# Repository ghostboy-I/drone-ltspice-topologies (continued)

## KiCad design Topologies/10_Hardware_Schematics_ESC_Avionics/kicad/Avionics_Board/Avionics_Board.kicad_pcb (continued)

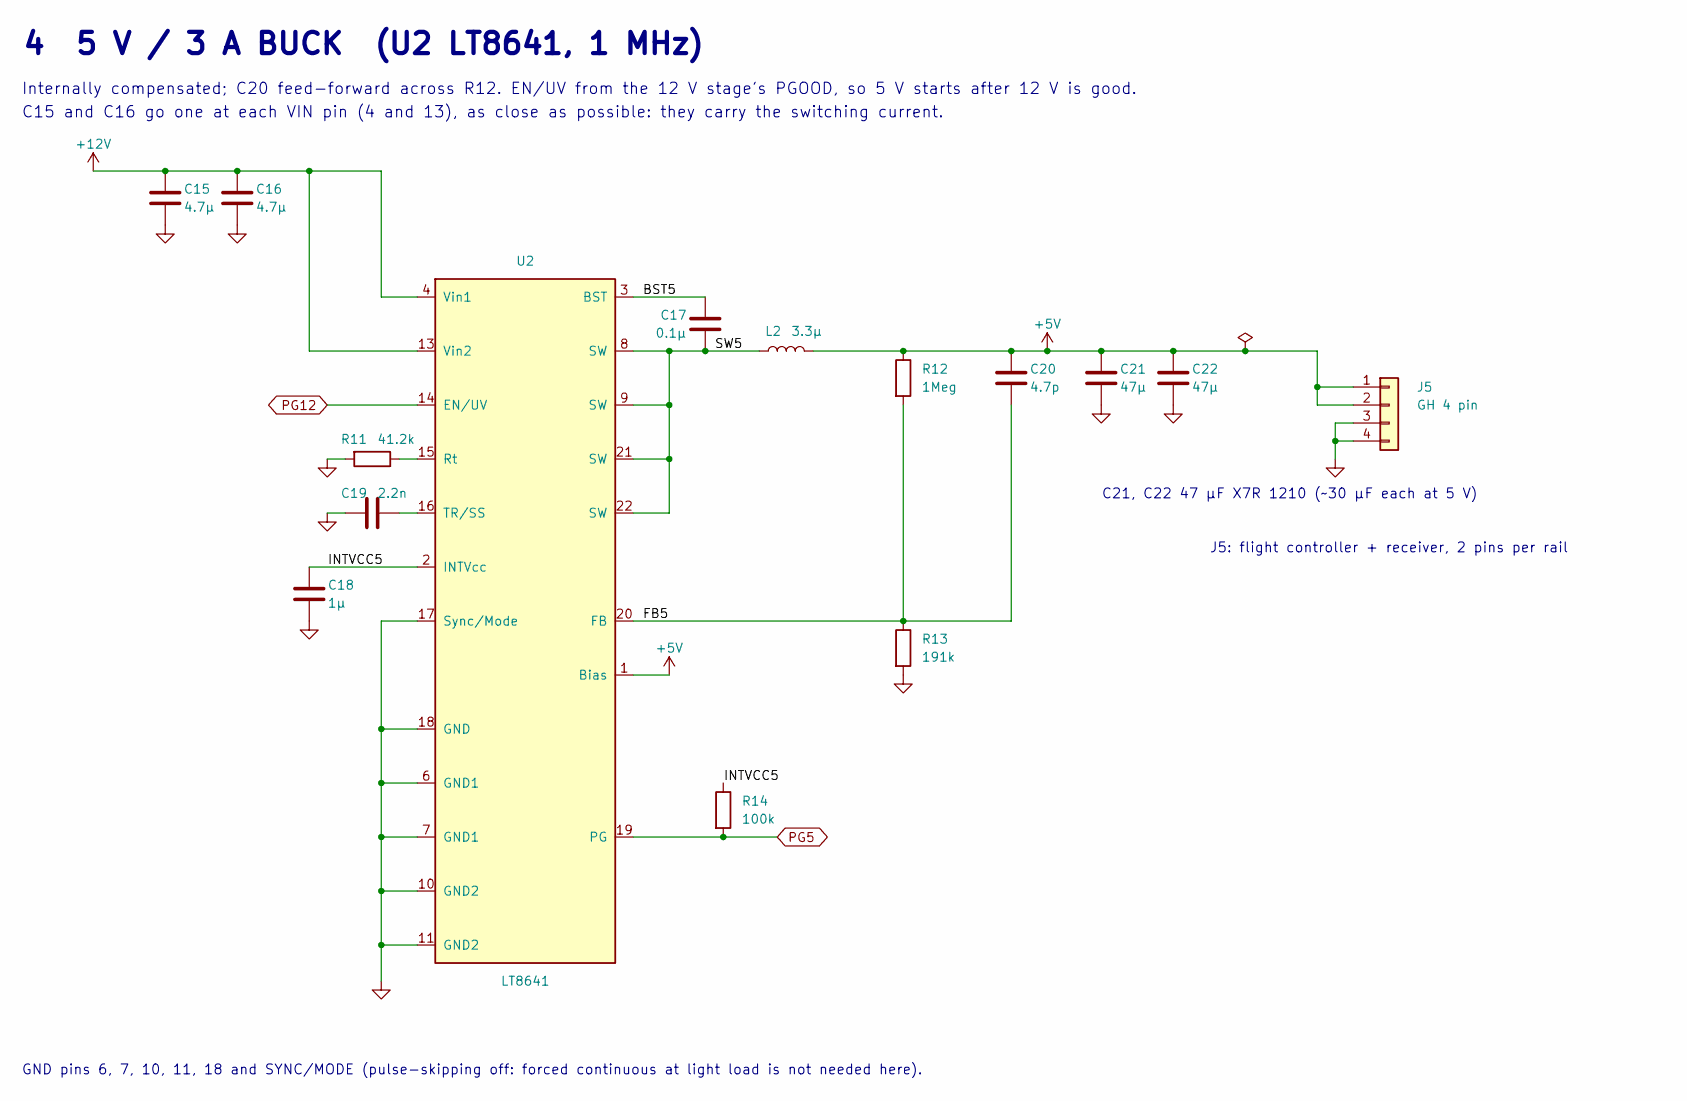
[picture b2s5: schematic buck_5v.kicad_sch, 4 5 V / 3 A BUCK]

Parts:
C15, C16: 4.7µ; C_0805_2012Metric; Rating 25 V; MPN/Spec X7R
C17: 0.1µ; C_0603_1608Metric; MPN/Spec X7R
C18: 1µ; C_0603_1608Metric; MPN/Spec X7R
C19: 2.2n; C_0603_1608Metric; MPN/Spec X7R
C20: 4.7p; C_0603_1608Metric; MPN/Spec X7R
C21, C22: 47µ; C_1210_3225Metric; Rating 10 V; MPN/Spec X7R 1210 (~30 µF at 5 V)
J5: GH 4 pin; JST_GH_BM04B-GHS-TBT_1x04-1MP_P1.25mm_Vertical; MPN/Spec JST GH 4 pin (2 pins per rail, 1 A/pin)
L2: 3.3µ; L_Coilcraft_XAL4020-XXX; Rating Isat 6 A; MPN/Spec shielded, Isat ≥ 6 A, DCR ≤ 10 mΩ
R11: 41.2k; R_0603_1608Metric; MPN/Spec 1 %, thick film
R12: 1Meg; R_0603_1608Metric; MPN/Spec 1 %, thick film
R13: 191k; R_0603_1608Metric; MPN/Spec 1 %, thick film
R14: 100k; R_0603_1608Metric; MPN/Spec 1 %, thick film
U2: LT8641; Linear_UDC-18-2EP_3x4mm_P0.5mm; Rating 65 V; MPN/Spec LT8641EUDC#PBF (UDC 20(18)-lead 3x4 mm 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

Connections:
+5V: C20.1, C21.1, C22.1, J5.1, J5.2, L2.2, R12.1, U2.1 (Bias); also elsewhere on the board
+12V: C15.1, C16.1, U2.4 (Vin1), U2.13 (Vin2); also elsewhere on the board
/Buck_5V/BST5: C17.1, U2.3 (BST)
/Buck_5V/FB5: C20.2, R12.2, R13.1, U2.20 (FB)
/Buck_5V/INTVCC5: C18.1, R14.1, U2.2 (INTVcc)
/Buck_5V/SW5: C17.2, L2.1, U2.8 (SW), U2.9 (SW), U2.21 (SW), U2.22 (SW)
GND: C15.2, C16.2, C18.2, C19.2, C21.2, C22.2, J5.3, J5.4, R11.2, R13.2, U2.6 (GND1), U2.7 (GND1), U2.10 (GND2), U2.11 (GND2), U2.17 (Sync/Mode), U2.18 (GND); also elsewhere on the board
unnamed: R11.1, U2.15 (Rt)
unnamed: C19.1, U2.16 (TR/SS)
PG5: R14.2, U2.19 (PG); also elsewhere on the board
PG12: U2.14 (EN/UV); also elsewhere on the board

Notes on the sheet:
4 5 V / 3 A BUCK (U2 LT8641, 1 MHz)
Internally compensated; C20 feed-forward across R12. EN/UV from the 12 V stage's PGOOD, so 5 V starts after 12 V is good.
C15 and C16 go one at each VIN pin (4 and 13), as close as possible: they carry the switching current.
GND pins 6, 7, 10, 11, 18 and SYNC/MODE (pulse-skipping off: forced continuous at light load is not needed here).
C21, C22 47 µF X7R 1210 (~30 µF each at 5 V)
J5: flight controller + receiver, 2 pins per rail

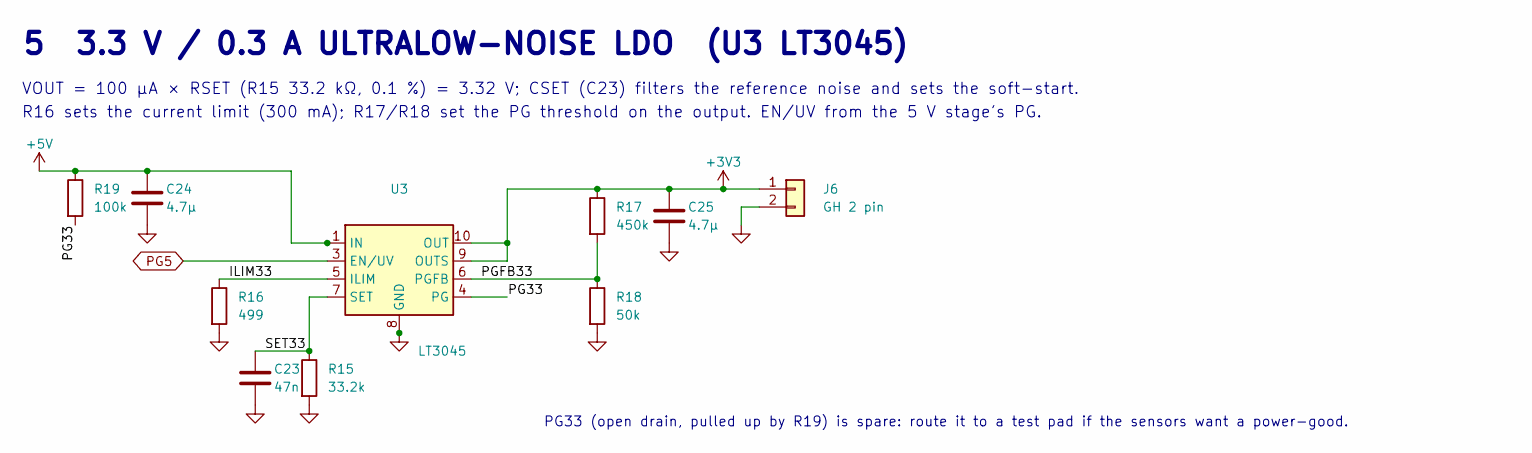
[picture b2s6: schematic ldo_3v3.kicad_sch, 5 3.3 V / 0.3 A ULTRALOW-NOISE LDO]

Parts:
C23: 47n; C_0603_1608Metric; MPN/Spec X7R
C24, C25: 4.7µ; C_0805_2012Metric; Rating 10 V; MPN/Spec X7R
J6: GH 2 pin; JST_GH_BM02B-GHS-TBT_1x02-1MP_P1.25mm_Vertical; MPN/Spec JST GH 2 pin
R15: 33.2k; R_0603_1608Metric; MPN/Spec 0.1 %, 25 ppm
R16: 499; R_0603_1608Metric; MPN/Spec 1 %, thick film
R17: 450k; R_0603_1608Metric; MPN/Spec 1 %, thick film
R18: 50k; R_0603_1608Metric; MPN/Spec 1 %, thick film
R19: 100k; R_0603_1608Metric; MPN/Spec 1 %, thick film
U3: LT3045; DFN-10-1EP_3x3mm_P0.5mm_EP1.65x2.38mm; Rating 20 V; MPN/Spec LT3045EDD (DFN-10 3x3)

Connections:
+3V3: C25.1, J6.1, R17.1, U3.9 (OUTS), U3.10 (OUT)
+5V: C24.1, R19.1, U3.1 (IN), U3.2 (IN); also elsewhere on the board
/LDO_3V3/ILIM33: R16.1, U3.5 (ILIM)
/LDO_3V3/PG33: R19.2, U3.4 (PG)
/LDO_3V3/PGFB33: R17.2, R18.1, U3.6 (PGFB)
/LDO_3V3/SET33: C23.1, R15.1, U3.7 (SET)
GND: C23.2, C24.2, C25.2, J6.2, R15.2, R16.2, R18.2, U3.8 (GND), U3.11 (GND); also elsewhere on the board
PG5: U3.3 (EN/UV); also elsewhere on the board

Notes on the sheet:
5 3.3 V / 0.3 A ULTRALOW-NOISE LDO (U3 LT3045)
VOUT = 100 µA × RSET (R15 33.2 kΩ, 0.1 %) = 3.32 V; CSET (C23) filters the reference noise and sets the soft-start.
R16 sets the current limit (300 mA); R17/R18 set the PG threshold on the output. EN/UV from the 5 V stage's PG.
PG33 (open drain, pulled up by R19) is spare: route it to a test pad if the sensors want a power-good.

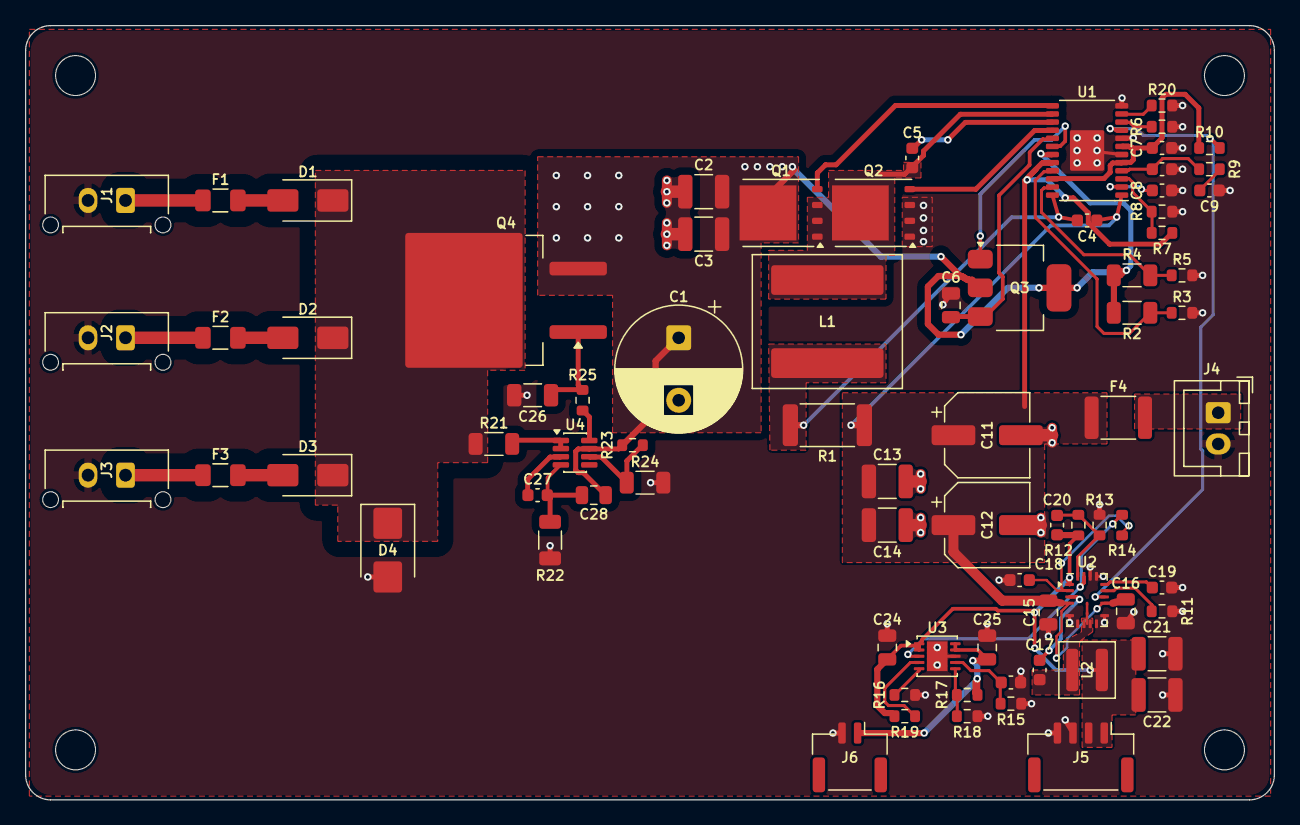
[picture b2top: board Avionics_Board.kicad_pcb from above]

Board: 4 copper layers, 100.0 x 62.0 mm, 81 parts (0 on the bottom side), 47 nets.

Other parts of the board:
H1, H2, H3, H4: M3; MountingHole_3.2mm_M3

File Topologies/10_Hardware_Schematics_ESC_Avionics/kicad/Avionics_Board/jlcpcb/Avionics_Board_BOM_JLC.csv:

Comment,Designator,Footprint,LCSC Part #
"33u Aluminium electrolytic, low ESR 160 V",C1,CP_Radial_D10.0mm_P5.00mm,
2.2u X7R 1210 250 V,"C2,C3",C_1210_3225Metric,
1n X7R,C4,C_0603_1608Metric,
0.1u X7R 25 V,C5,C_0603_1608Metric,
4.7u X7R 25 V,"C6,C15,C16",C_0805_2012Metric,
0.1u X7R,"C7,C17",C_0603_1608Metric,
33n X7R,C8,C_0603_1608Metric,
15n X7R,C9,C_0603_1608Metric,
330p X7R,C10,C_0603_1608Metric,
"47u Polymer, ESR <= 15 mR 25 V","C11,C12",CP_Elec_6.3x7.7,
10u 10 uF X7R 1210 (5 uF at 12 V bias) 25 V,"C13,C14",C_1210_3225Metric,
1u X7R,C18,C_0603_1608Metric,
2.2n X7R,C19,C_0603_1608Metric,
4.7p X7R,C20,C_0603_1608Metric,
47u X7R 1210 (~30 uF at 5 V) 10 V,"C21,C22",C_1210_3225Metric,
47n X7R,C23,C_0603_1608Metric,
4.7u X7R 10 V,"C24,C25",C_0805_2012Metric,
10n X7R 1206 250 V (e.g. Murata GRM31BR72E103KW01) 250 V,C26,C_1206_3216Metric,
180n X7R,C27,C_0603_1608Metric,
470n X7R 25 V,C28,C_0805_2012Metric,
ES1D ES1D 200 V 1 A,"D1,D2,D3",D_SMA,
SMBJ110A SMBJ110A VBR 122 V,D4,D_SMB,
"0.5 A Littelfuse 0451.500 (NANO2, 125 V DC) 125 V DC","F1,F2,F3",Fuse_1206_3216Metric,
"2 A Bourns MF-MSMF200 (1812) 2 A hold, 16 V",F4,Fuse_1812_4532Metric,
"Micro-Fit 3.0 Molex Micro-Fit 3.0, 2 pin (600 V, 5 A) >=150 V","J1,J2,J3",Molex_Micro-Fit_3.0_43650-0215_1x02_P3.00mm_Vertical,
XH 2 pin JST XH 2 pin (3 A),J4,JST_XH_B2B-XH-A_1x02_P2.50mm_Vertical,
"GH 4 pin JST GH 4 pin (2 pins per rail, 1 A/pin)",J5,JST_GH_BM04B-GHS-TBT_1x04-1MP_P1.25mm_Vertical,
GH 2 pin JST GH 2 pin,J6,JST_GH_BM02B-GHS-TBT_1x02-1MP_P1.25mm_Vertical,
"47u shielded 10x10 mm (e.g. Coilcraft XAL1010 family), Isat >= 9.2 A, DCR <= 30 mR Isat 9.2 A",L1,L_Coilcraft_XAL1010-XXX,
"3.3u shielded, Isat >= 6 A, DCR <= 10 mR Isat 6 A",L2,L_Coilcraft_XAL4020-XXX,
BSC520N15NS3 Infineon BSC520N15NS3 150 V 21 A,Q1,TDSON-8-1,
BSC360N15NS3 Infineon BSC360N15NS3 150 V 30 A,Q2,TDSON-8-1,
BSP89 Infineon BSP89 240 V,Q3,SOT-223-3_TabPin2,
"FDB33N25 onsemi FDB33N25 (250 V, 94 mR, D2PAK) 250 V 33 A",Q4,TO-263-2,
"10m current sense, 1 %, 1 W 1 W",R1,R_2512_6332Metric,
"976k 1 %, thick film 200 V",R2,R_1206_3216Metric,
"20k 1 %, thick film",R3,R_0603_1608Metric,
"1Meg 1 %, thick film 200 V",R4,R_1206_3216Metric,
"10.2k 1 %, thick film",R5,R_0603_1608Metric,
"30.1k 1 %, thick film",R6,R_0603_1608Metric,
"140k 1 %, thick film",R7,R_0603_1608Metric,
"10k 1 %, thick film",R8,R_0603_1608Metric,
"6.98k 1 %, thick film",R9,R_0603_1608Metric,
"100k 1 %, thick film","R10,R14,R19,R20",R_0603_1608Metric,
"41.2k 1 %, thick film",R11,R_0603_1608Metric,
"1Meg 1 %, thick film",R12,R_0603_1608Metric,
"191k 1 %, thick film",R13,R_0603_1608Metric,
"33.2k 0.1 %, 25 ppm",R15,R_0603_1608Metric,
"499 1 %, thick film",R16,R_0603_1608Metric,
"450k 1 %, thick film",R17,R_0603_1608Metric,
"50k 1 %, thick film",R18,R_0603_1608Metric,
"2.49Meg 1 %, thick film 200 V",R21,R_1206_3216Metric,
"274k 1 %, thick film 200 V",R22,R_1206_3216Metric,
"12.4k 1 %, thick film",R23,R_0603_1608Metric,
"1.15Meg 1 %, thick film 200 V",R24,R_1206_3216Metric,
"10 1 %, thick film",R25,R_0603_1608Metric,
LTC7801 LTC7801EFE (TSSOP-24 with exposed pad) 150 V,U1,Linear_HTSSOP-24-1EP_4.4x7.8mm_P0.65mm_EP2.74x3.25mm,
LT8641 LT8641EUDC#PBF (UDC 20(18)-lead 3x4 mm QFN) 65 V,U2,Linear_UDC-18-2EP_3x4mm_P0.5mm,
LT3045 LT3045EDD (DFN-10 3x3) 20 V,U3,DFN-10-1EP_3x3mm_P0.5mm_EP1.65x2.38mm,
LTC4366-2 LTC4366CTS8-2 (TSOT-23-8) 9 V to >500 V (floating),U4,TSOT-23-8,
